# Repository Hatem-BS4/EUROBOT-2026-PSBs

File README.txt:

# EUROBOT 2026 PCBs

Repository containing PCB design files for the Eurobot 2026 competition.

Author: Hatem Ben Salha
GitHub: https://github.com/Hatem-BS4
LinkedIn: https://linkedin.com/in/hatem-ben-salha

---

## Repository Contents

**carte distribution/**
- Component distribution files and circuit schematics

**Carte Mosfet/**
- MOSFET driver PCB design files
- Schematics and board layouts

**Carte servo/**
- Servo motor control PCB designs
- PWM signal conditioning circuits

**ESP motors - 2.0/**
- ESP32-based motor control v2.0
- Firmware and hardware integration
- Communication protocols for competition robot

**Pami_ESP32/**
- Primary ESP32 board design
- Main controller for the competition robot
- Sensor integration interfaces

**Gerbers/**
- PCB manufacturing files (Gerber format)
- Drill files and layer specifications
- Ready for PCB fabrication

---

## Project Context

These PCB designs were developed as part of the Eurobot 2026 competition, an international robotics competition for engineering students.

The designs include:
- Custom motor drivers for competition robot actuation
- Sensor interface circuits for vision and obstacle detection
- ESP32-based communication modules for wireless control
- Power management circuits for battery optimization
- Modular design approach for rapid prototyping and iteration

## Technical Details

**Software Used:**
- KiCad EDA (for schematic capture and PCB layout)
- Gerber format for PCB manufacturing
- Embedded C/Firmware for ESP32 microcontroller

**Hard Platform:**
- STM32/ESP32 microcontrollers (as per competition requirements)
- Custom 2-4 layer PCBs for optimal signal integrity
- Surface-mount components for compact design

## Getting Started

1. Clone the repository to explore the design files:
   ```bash
   git clone https://github.com/Hatem-BS4/EUROBOT-2026-PCBs.git

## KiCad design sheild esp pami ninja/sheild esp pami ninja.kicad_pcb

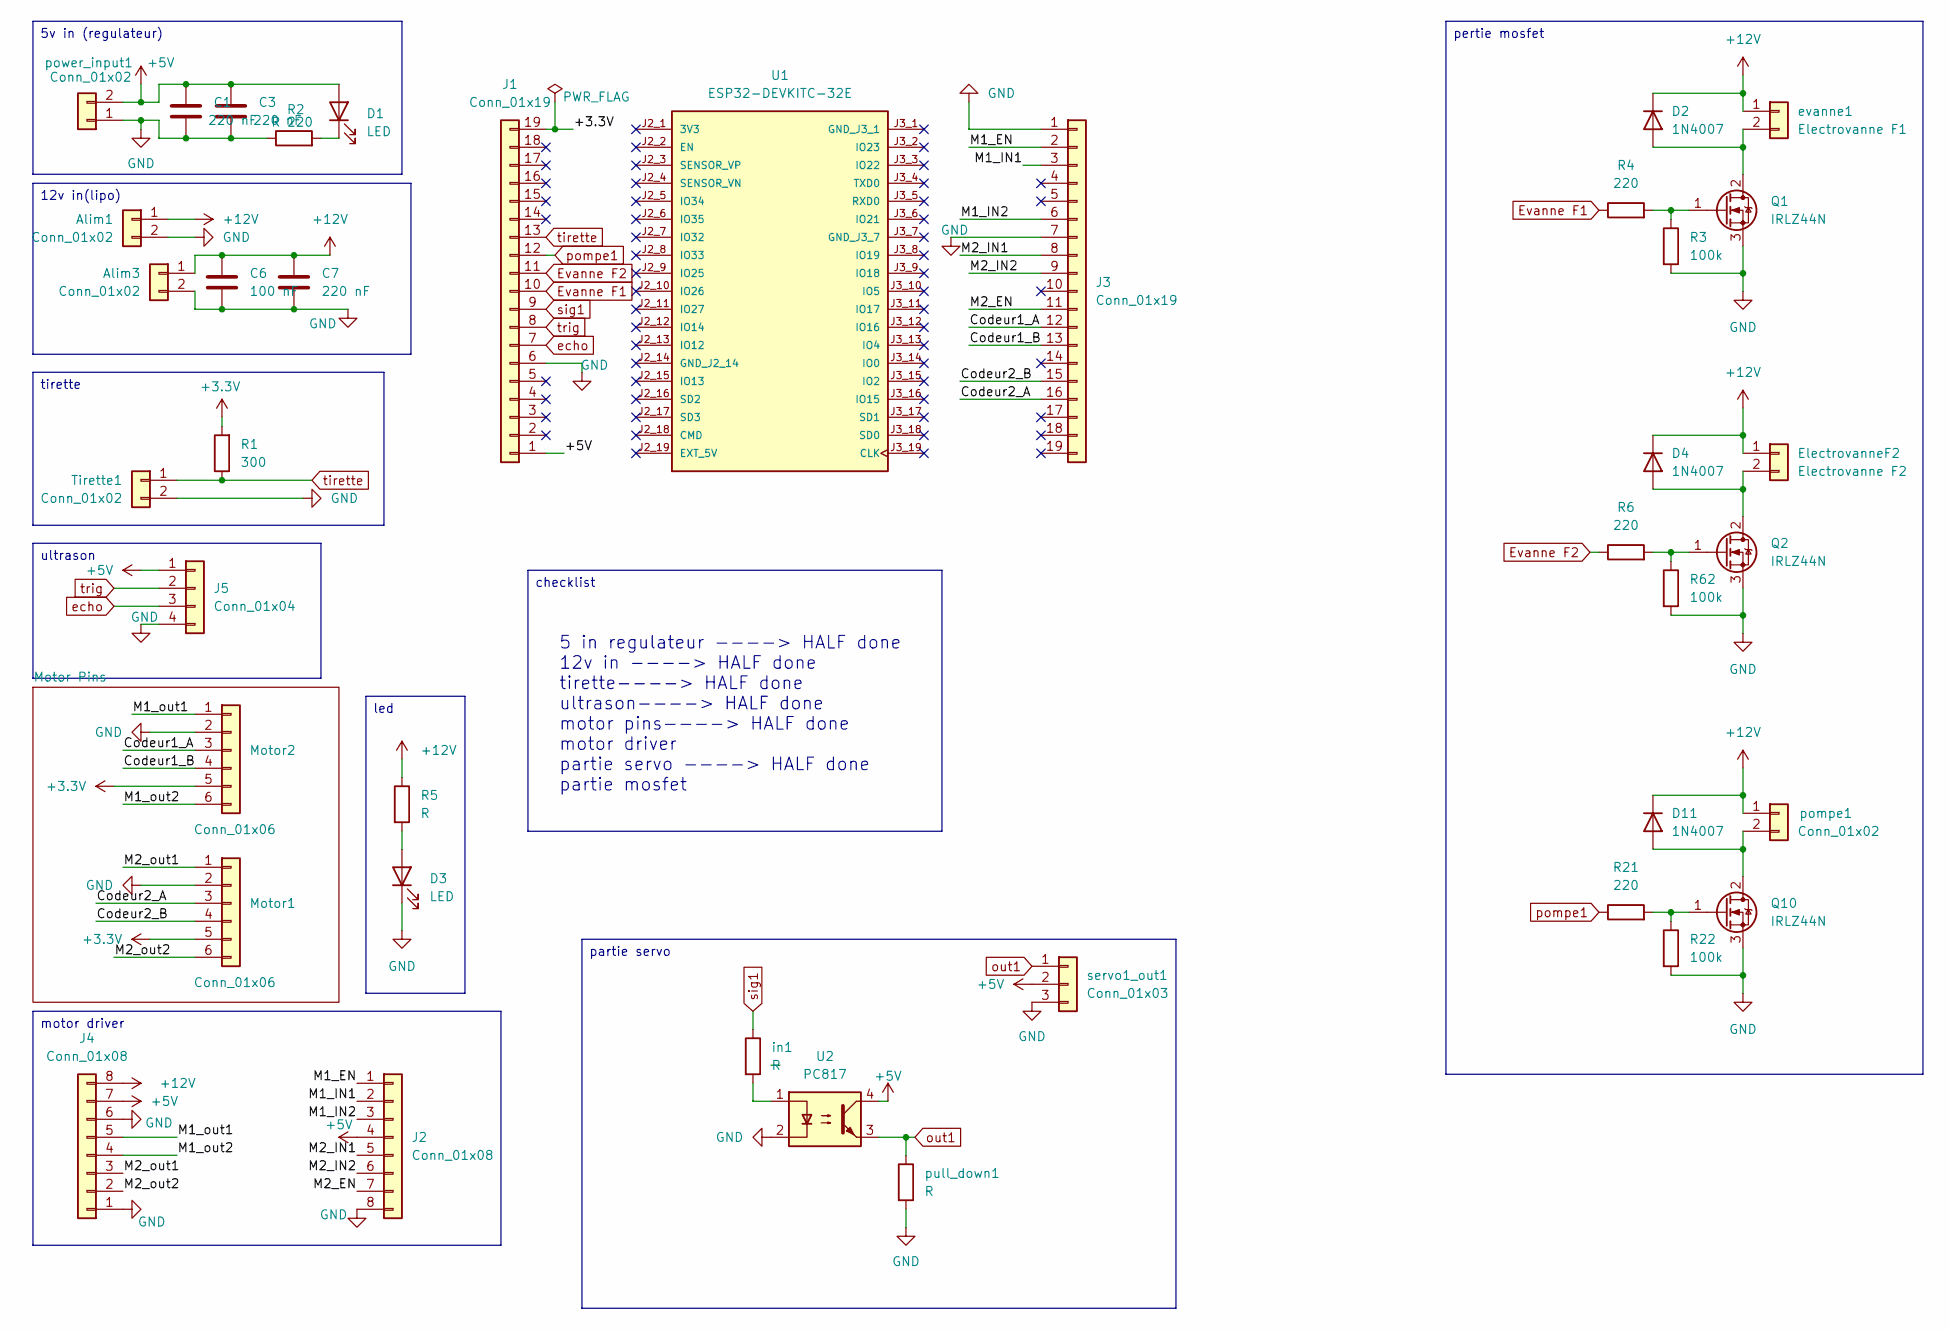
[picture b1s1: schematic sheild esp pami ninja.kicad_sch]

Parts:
Alim1, Alim3: Conn_01x02; TerminalBlock_MaiXu_MX126-5.0-02P_1x02_P5.00mm
C1, C3, C7: 220 nF; C_Radial_D6.3mm_H5.0mm_P2.50mm
C6: 100 nF; C_Radial_D6.3mm_H5.0mm_P2.50mm
D1, D3: LED; LED_D4.0mm
D2, D4, D11: 1N4007; D_DO-41_SOD81_P10.16mm_Horizontal
ElectrovanneF2: Electrovanne F2; JST_XH_B2B-XH-A_1x02_P2.50mm_Vertical
J1, J3: Conn_01x19; PinSocket_1x19_P2.54mm_Vertical
J2, J4: Conn_01x08; PinSocket_1x08_P2.54mm_Vertical
J5: Conn_01x04; PinHeader_1x04_P2.54mm_Vertical
Motor1, Motor2: Conn_01x06; PinHeader_1x06_P2.54mm_Vertical
Q1, Q2, Q10: IRLZ44N; TO-220-3_Vertical
R1: 300; R_Axial_DIN0207_L6.3mm_D2.5mm_P7.62mm_Horizontal
R2: R 220; R_Axial_DIN0207_L6.3mm_D2.5mm_P7.62mm_Horizontal
R3, R22, R62: 100k; R_Axial_DIN0207_L6.3mm_D2.5mm_P7.62mm_Horizontal
R4, R6, R21: 220; R_Axial_DIN0207_L6.3mm_D2.5mm_P7.62mm_Horizontal
R5: R; R_Axial_DIN0207_L6.3mm_D2.5mm_P7.62mm_Horizontal
Tirette1: Conn_01x02; PinHeader_1x02_P2.54mm_Vertical
U1: ESP32-DEVKITC-32E; PARTREV 1.4
U2: PC817; DIP-4_W7.62mm
evanne1: Electrovanne F1; JST_XH_B2B-XH-A_1x02_P2.50mm_Vertical
in1: R; R_Axial_DIN0207_L6.3mm_D2.5mm_P7.62mm_Horizontal
pompe1: Conn_01x02; JST_XH_B2B-XH-A_1x02_P2.50mm_Vertical
power_input1: Conn_01x02; TerminalBlock_MaiXu_MX126-5.0-02P_1x02_P5.00mm
pull_down1: R; R_Axial_DIN0207_L6.3mm_D2.5mm_P7.62mm_Horizontal
servo1_out1: Conn_01x03; PinHeader_1x03_P2.54mm_Vertical

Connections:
+3.3V: J1.19, Motor1.5, Motor2.5, R1.2
+5V: C1.1, C3.1, D1.2 (A), J1.1, J2.4, J4.7, J5.1, U2.4, power_input1.2, servo1_out1.2
+12V: Alim1.1, Alim3.1, C6.1, C7.1, D2.1 (K), D4.1 (K), D11.1 (K), ElectrovanneF2.1, J4.8, R5.1, evanne1.1, pompe1.1
/Codeur1_A: J3.12, Motor2.3
/Codeur1_B: J3.13, Motor2.4
/Codeur2_A: J3.16, Motor1.3
/Codeur2_B: J3.15, Motor1.4
/M1_EN: J2.1, J3.2
/M1_IN1: J2.2, J3.3
/M1_IN2: J2.3, J3.6
/M1_out1: J4.5, Motor2.1
/M1_out2: J4.4, Motor2.6
/M2_EN: J2.7, J3.11
/M2_IN1: J2.5, J3.8
/M2_IN2: J2.6, J3.9
/M2_out1: J4.3, Motor1.1
/M2_out2: J4.2, Motor1.6
Evanne F1: J1.10, R4.1
Evanne F2: J1.11, R6.1
GND: Alim1.2, Alim3.2, C1.2, C3.2, C6.2, C7.2, D3.1 (K), J1.6, J2.8, J3.1, J3.7, J4.1, J4.6, J5.4, Motor1.2, Motor2.2, Q1.3 (S), Q2.3 (S), Q10.3 (S), R2.1, R3.2, R22.2, R62.2, Tirette1.2, U2.2, power_input1.1, pull_down1.2, servo1_out1.3
unnamed: D1.1 (K), R2.2
unnamed: D2.2 (A), Q1.2 (D), evanne1.2
unnamed: D3.2 (A), R5.2
unnamed: D4.2 (A), ElectrovanneF2.2, Q2.2 (D)
unnamed: D11.2 (A), Q10.2 (D), pompe1.2
unnamed: Q1.1 (G), R3.1, R4.2
unnamed: Q2.1 (G), R6.2, R62.1
unnamed: Q10.1 (G), R21.2, R22.1
unnamed: U2.1, in1.2
echo: J1.7, J5.3
out1: U2.3, pull_down1.1, servo1_out1.1
pompe1: J1.12, R21.1
sig1: J1.9, in1.1
tirette: J1.13, R1.1, Tirette1.1
trig: J1.8, J5.2

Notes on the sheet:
5 in regulateur ----> HALF done 12v in ----> HALF done tirette----> HALF done ultrason----> HALF done motor pins----> HALF done motor driver partie servo ----> HALF done partie mosfet
pertie mosfet
5v in (regulateur)
checklist
ultrason
tirette
led
12v in(lipo)
partie servo
motor driver

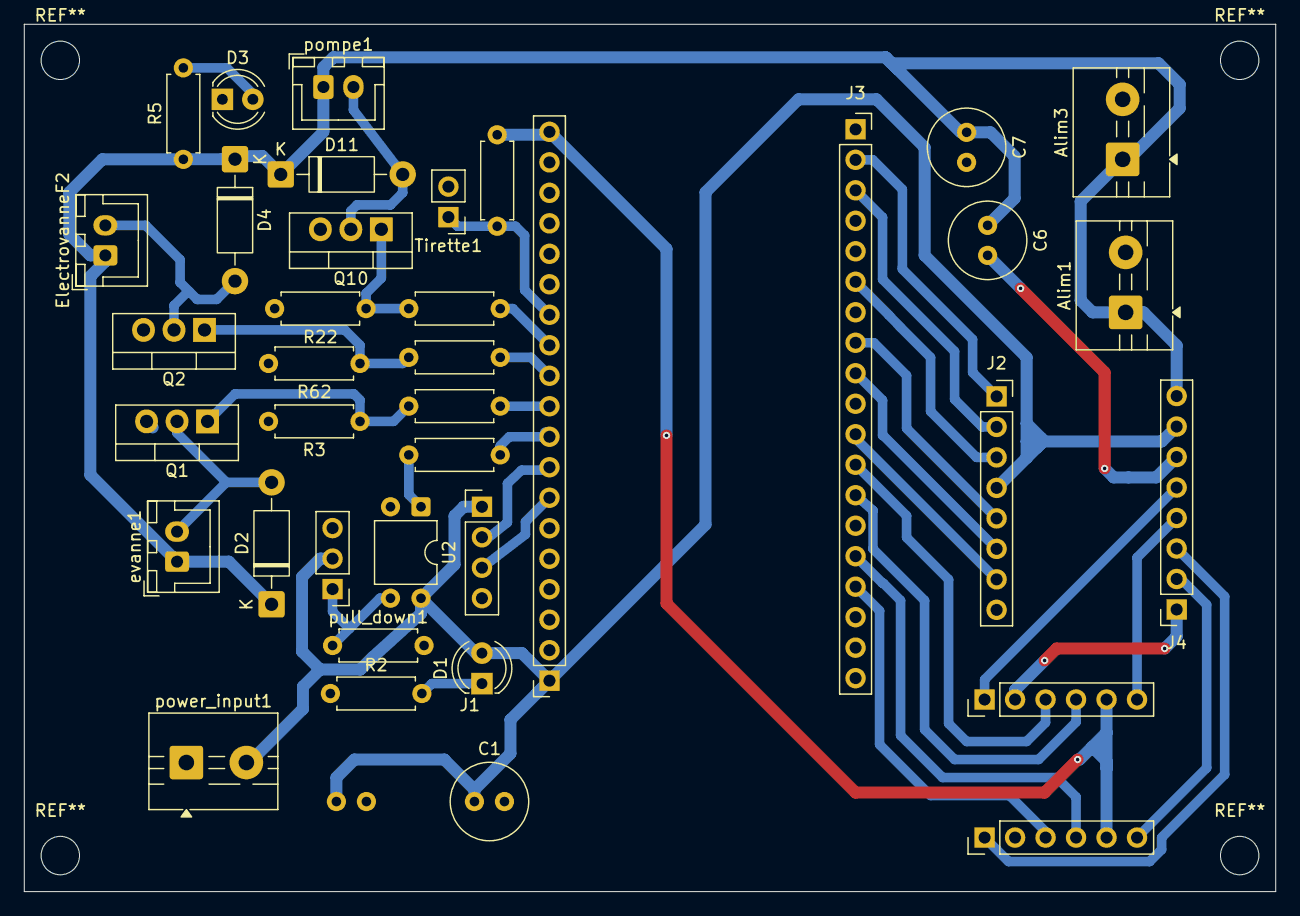
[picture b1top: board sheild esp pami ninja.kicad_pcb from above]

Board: 2 copper layers, 104.2 x 72.2 mm, 39 parts (1 on the bottom side), 35 nets.

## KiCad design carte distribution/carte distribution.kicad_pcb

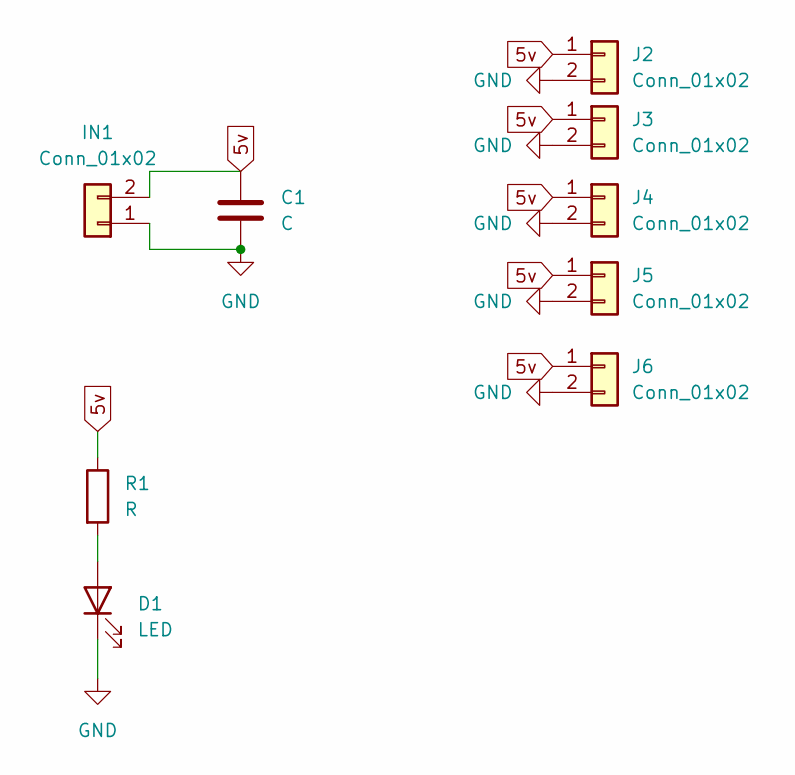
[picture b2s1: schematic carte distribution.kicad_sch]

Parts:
C1: C; C_Radial_D6.3mm_H5.0mm_P2.50mm
D1: LED; LED_D4.0mm
IN1: Conn_01x02; TerminalBlock_MaiXu_MX126-5.0-02P_1x02_P5.00mm
J2, J3, J4, J5, J6: Conn_01x02; TerminalBlock_MaiXu_MX126-5.0-02P_1x02_P5.00mm
R1: R; R_Axial_DIN0207_L6.3mm_D2.5mm_P7.62mm_Horizontal

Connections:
5v: C1.1, IN1.2, J2.1, J3.1, J4.1, J5.1, J6.1, R1.1
GND: C1.2, D1.1 (K), IN1.1, J2.2, J3.2, J4.2, J5.2, J6.2
unnamed: D1.2 (A), R1.2

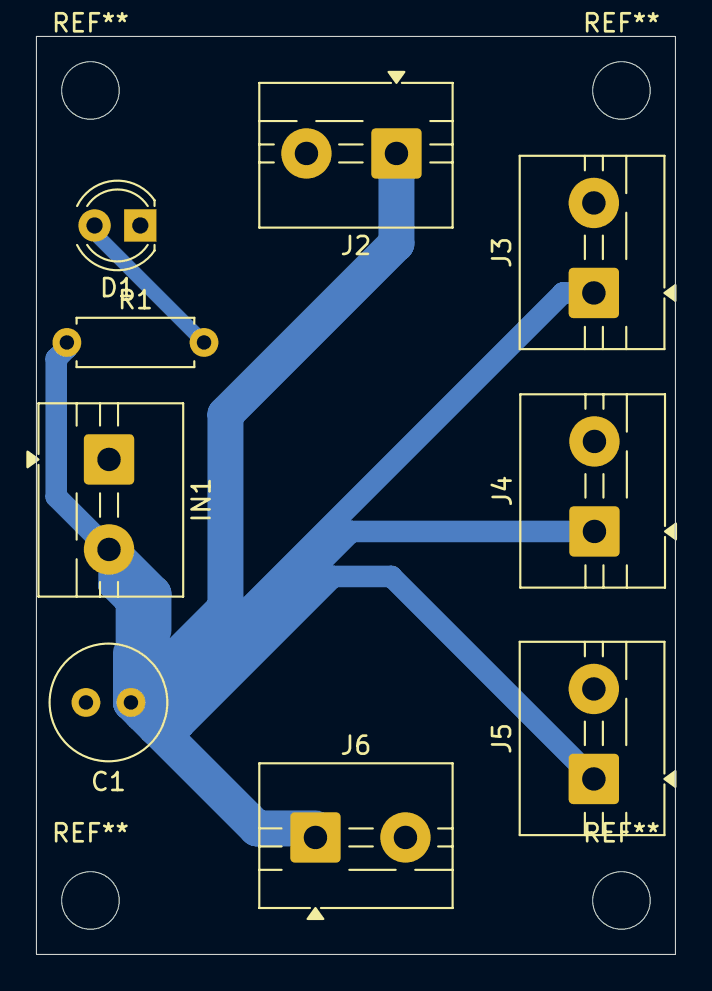
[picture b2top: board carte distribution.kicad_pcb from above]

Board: 2 copper layers, 35.5 x 51.0 mm, 9 parts (0 on the bottom side), 3 nets.

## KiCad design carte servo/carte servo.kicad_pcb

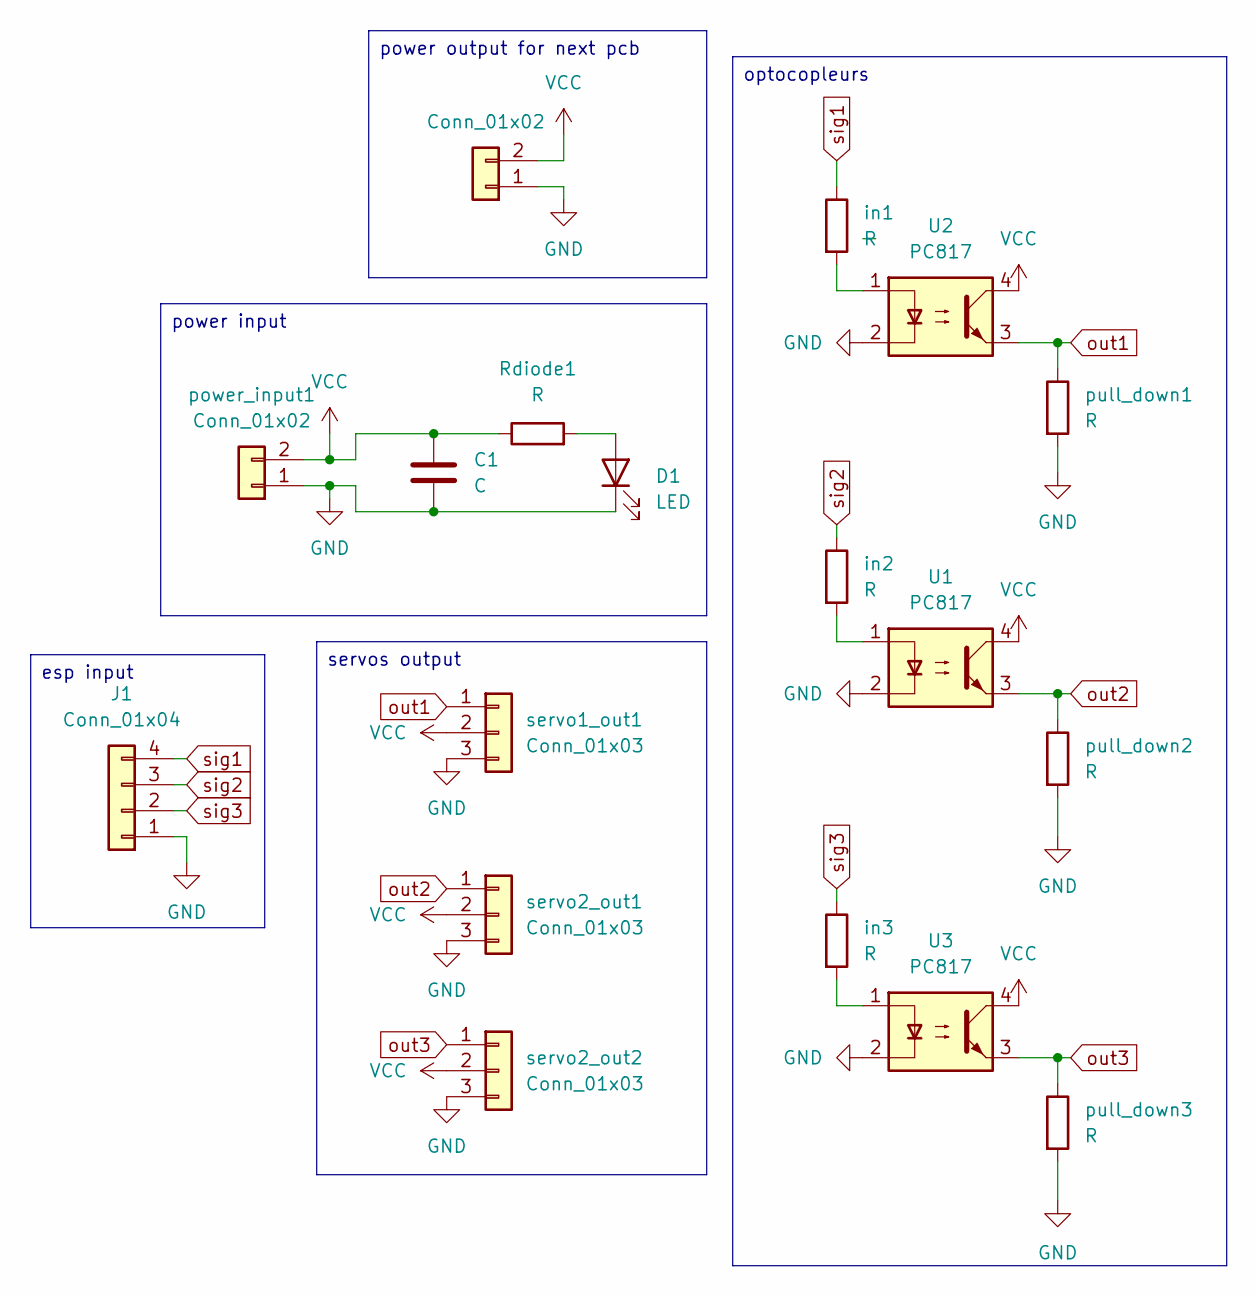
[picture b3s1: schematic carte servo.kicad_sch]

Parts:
C1: C; C_Radial_D6.3mm_H5.0mm_P2.50mm
D1: LED; LED_D4.0mm
J1: Conn_01x04; PinHeader_1x04_P2.54mm_Vertical
Rdiode1: R; R_Axial_DIN0207_L6.3mm_D2.5mm_P7.62mm_Horizontal
U1, U2, U3: PC817; DIP-4_W7.62mm
in1, in2, in3: R; R_Axial_DIN0207_L6.3mm_D2.5mm_P7.62mm_Horizontal
power_input1: Conn_01x02; TerminalBlock_MaiXu_MX126-5.0-02P_1x02_P5.00mm
power_output1: Conn_01x02; TerminalBlock_MaiXu_MX126-5.0-02P_1x02_P5.00mm
pull_down1, pull_down2, pull_down3: R; R_Axial_DIN0207_L6.3mm_D2.5mm_P7.62mm_Horizontal
servo1_out1, servo2_out1, servo2_out2: Conn_01x03; PinHeader_1x03_P2.54mm_Vertical

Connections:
GND: C1.2, D1.1 (K), J1.1, U1.2, U2.2, U3.2, power_input1.1, power_output1.1, pull_down1.2, pull_down2.2, pull_down3.2, servo1_out1.3, servo2_out1.3, servo2_out2.3
unnamed: D1.2 (A), Rdiode1.2
unnamed: U1.1, in2.2
unnamed: U2.1, in1.2
unnamed: U3.1, in3.2
VCC: C1.1, Rdiode1.1, U1.4, U2.4, U3.4, power_input1.2, power_output1.2, servo1_out1.2, servo2_out1.2, servo2_out2.2
out1: U2.3, pull_down1.1, servo1_out1.1
out2: U1.3, pull_down2.1, servo2_out1.1
out3: U3.3, pull_down3.1, servo2_out2.1
sig1: J1.4, in1.1
sig2: J1.3, in2.1
sig3: J1.2, in3.1

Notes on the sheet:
power input
optocopleurs
esp input
servos output
power output for next pcb

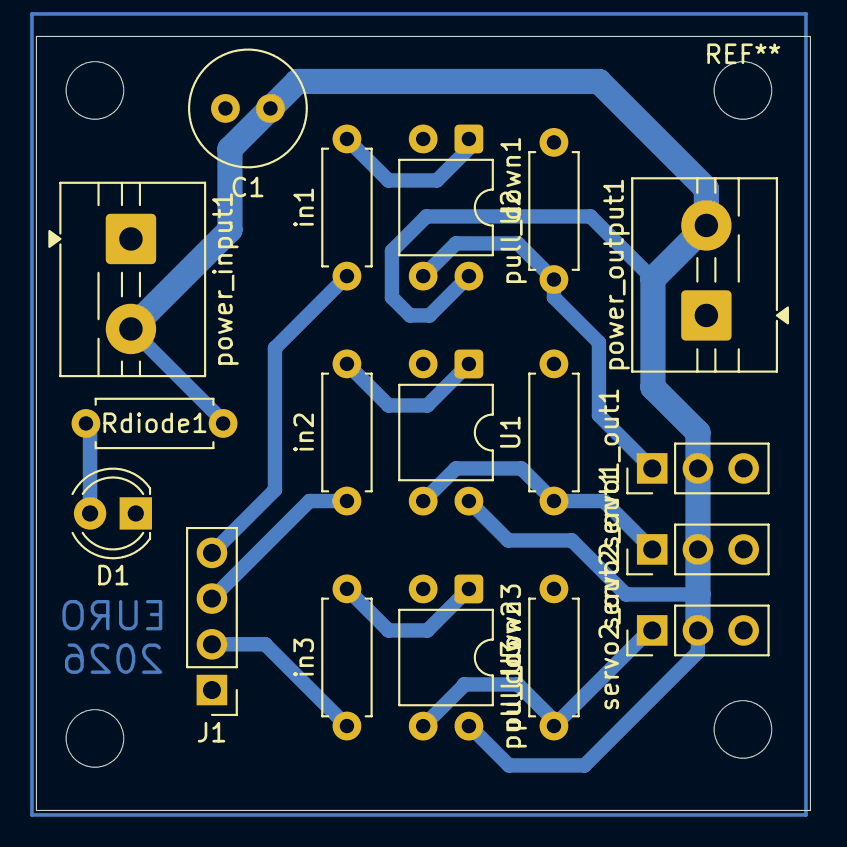
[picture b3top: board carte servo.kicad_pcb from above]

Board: 2 copper layers, 43.0 x 43.0 mm, 18 parts (0 on the bottom side), 12 nets.

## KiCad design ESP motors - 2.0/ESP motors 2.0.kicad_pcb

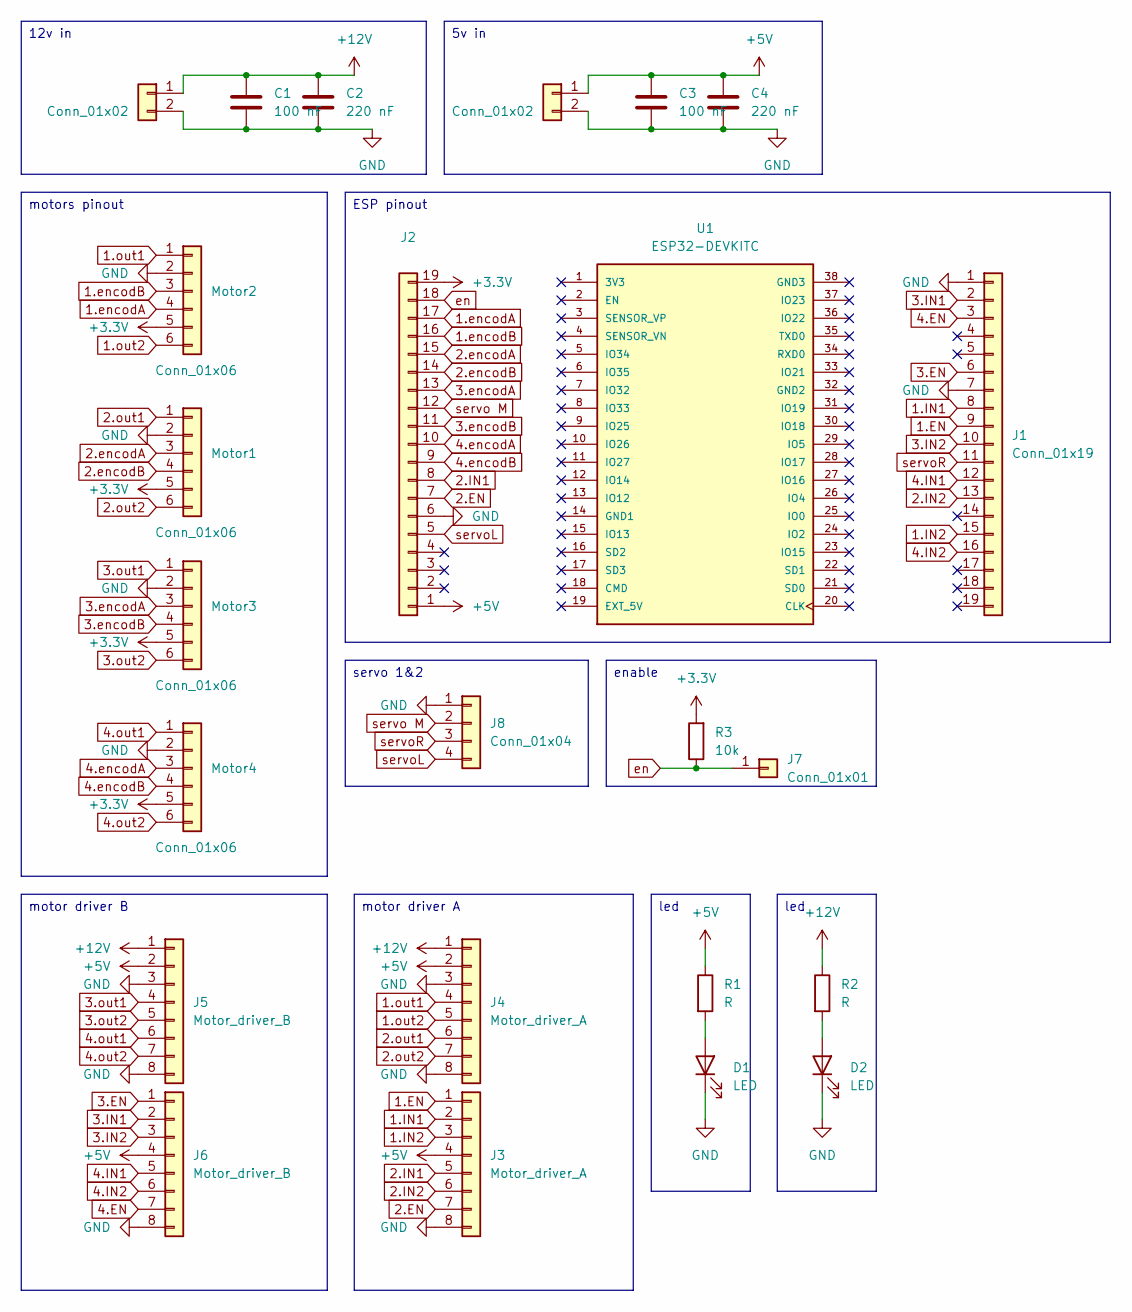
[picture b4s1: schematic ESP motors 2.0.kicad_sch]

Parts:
Alim1, Alim2: Conn_01x02; TerminalBlock_MaiXu_MX126-5.0-02P_1x02_P5.00mm
C1, C3: 100 nF; C_Radial_D6.3mm_H5.0mm_P2.50mm
C2, C4: 220 nF; C_Radial_D6.3mm_H5.0mm_P2.50mm
D1, D2: LED; LED_D4.0mm
J1, J2: Conn_01x19; PinSocket_1x19_P2.54mm_Vertical
J3, J4: Motor_driver_A; PinSocket_1x08_P2.54mm_Vertical
J5, J6: Motor_driver_B; PinSocket_1x08_P2.54mm_Vertical
J7: Conn_01x01; JST_XH_B2B-XH-A_1x02_P2.50mm_Vertical
J8: Conn_01x04; PinHeader_1x04_P2.54mm_Vertical
Motor1, Motor2, Motor3, Motor4: Conn_01x06; PinHeader_1x06_P2.54mm_Vertical
R1, R2: R; R_Axial_DIN0207_L6.3mm_D2.5mm_P7.62mm_Horizontal
R3: 10k; R_Axial_DIN0207_L6.3mm_D2.5mm_P7.62mm_Horizontal
U1: ESP32-DEVKITC; MODULE_ESP32-DEVKITC; PARTREV N/A

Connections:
1.EN: J1.9, J3.1
1.IN1: J1.8, J3.2
1.IN2: J1.15, J3.3
1.encodA: J2.17, Motor2.4
1.encodB: J2.16, Motor2.3
1.out1: J4.4, Motor2.1
1.out2: J4.5, Motor2.6
2.EN: J2.7, J3.7
2.IN1: J2.8, J3.5
2.IN2: J1.13, J3.6
2.encodA: J2.15, Motor1.3
2.encodB: J2.14, Motor1.4
2.out1: J4.6, Motor1.1
2.out2: J4.7, Motor1.6
3.EN: J1.6, J6.1
3.IN1: J1.2, J6.2
3.IN2: J1.10, J6.3
3.encodA: J2.13, Motor3.3
3.encodB: J2.11, Motor3.4
3.out1: J5.4, Motor3.1
3.out2: J5.5, Motor3.6
4.EN: J1.3, J6.7
4.IN1: J1.12, J6.5
4.IN2: J1.16, J6.6
4.encodA: J2.10, Motor4.3
4.encodB: J2.9, Motor4.4
4.out1: J5.6, Motor4.1
4.out2: J5.7, Motor4.6
+3.3V: J2.19, Motor1.5, Motor2.5, Motor3.5, Motor4.5, R3.2
+5V: Alim2.1, C3.1, C4.1, J2.1, J3.4, J4.2, J5.2, J6.4, R1.1
+12V: Alim1.1, C1.1, C2.1, J4.1, J5.1, R2.1
GND: Alim1.2, Alim2.2, C1.2, C2.2, C3.2, C4.2, D1.1 (K), D2.1 (K), J1.1, J1.7, J2.6, J3.8, J4.3, J4.8, J5.3, J5.8, J6.8, J8.1, Motor1.2, Motor2.2, Motor3.2, Motor4.2
unnamed: D1.2 (A), R1.2
unnamed: D2.2 (A), R2.2
en: J2.18, J7.1, R3.1
servo M: J2.12, J8.2
servoL: J2.5, J8.4
servoR: J1.11, J8.3

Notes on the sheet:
motor driver B
led
12v in
5v in
enable
motor driver A
servo 1&2
motors pinout
ESP pinout

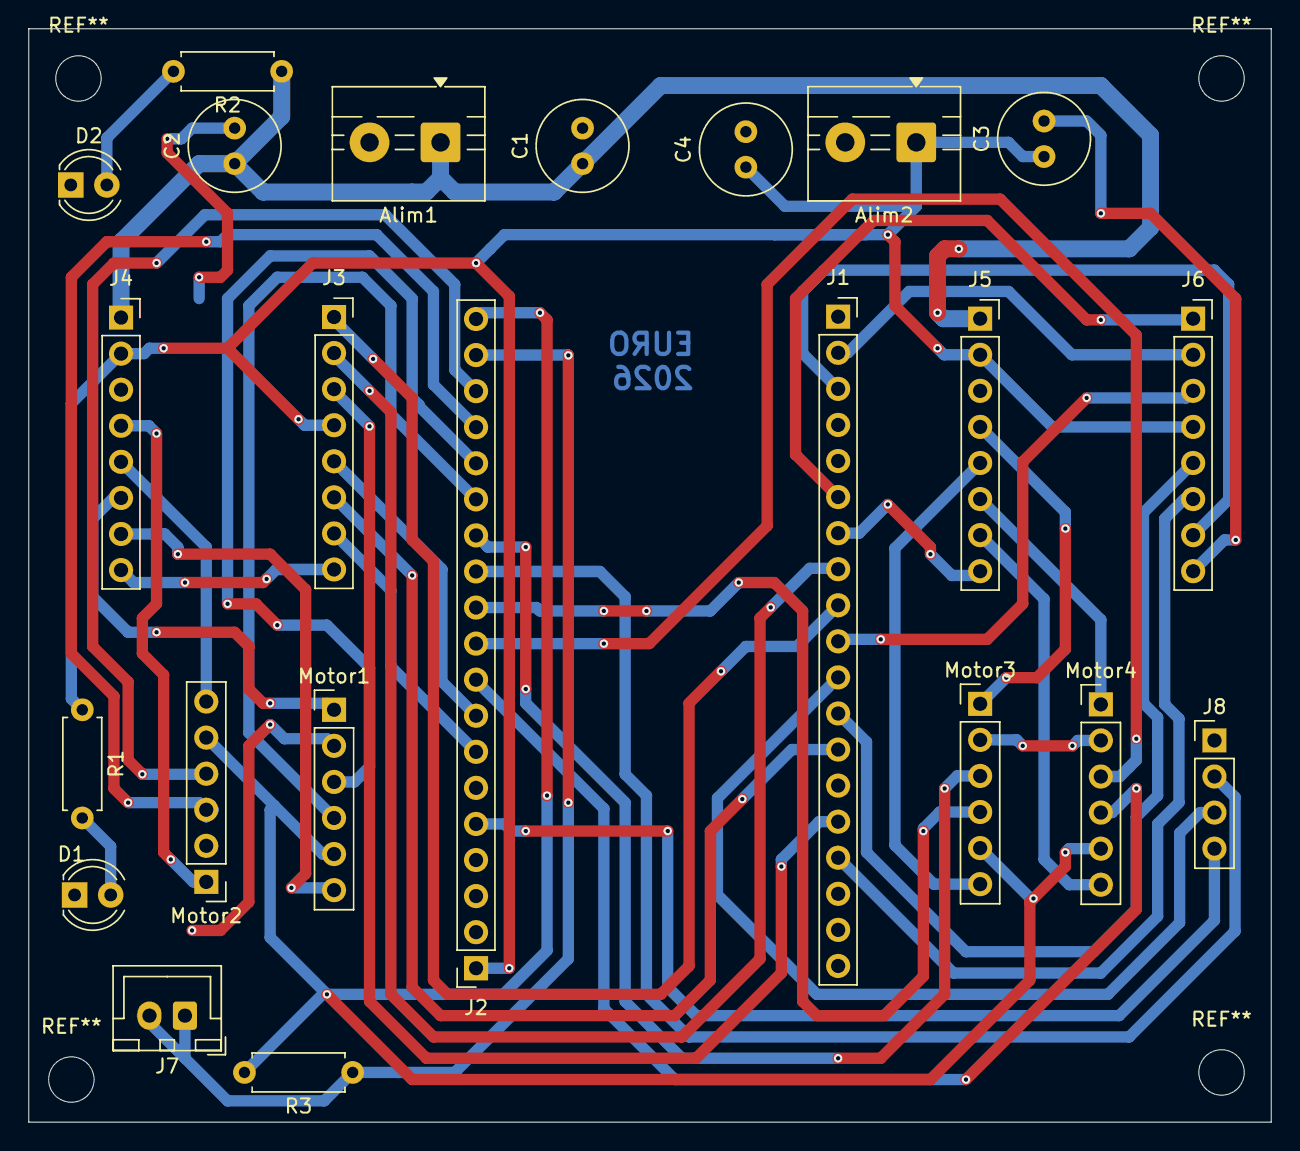
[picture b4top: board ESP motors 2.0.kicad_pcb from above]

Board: 2 copper layers, 87.5 x 77.0 mm, 23 parts (0 on the bottom side), 38 nets.

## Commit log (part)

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2026-01-19 zet sheild pami ninja
2026-02-05 pcbs+ninja
